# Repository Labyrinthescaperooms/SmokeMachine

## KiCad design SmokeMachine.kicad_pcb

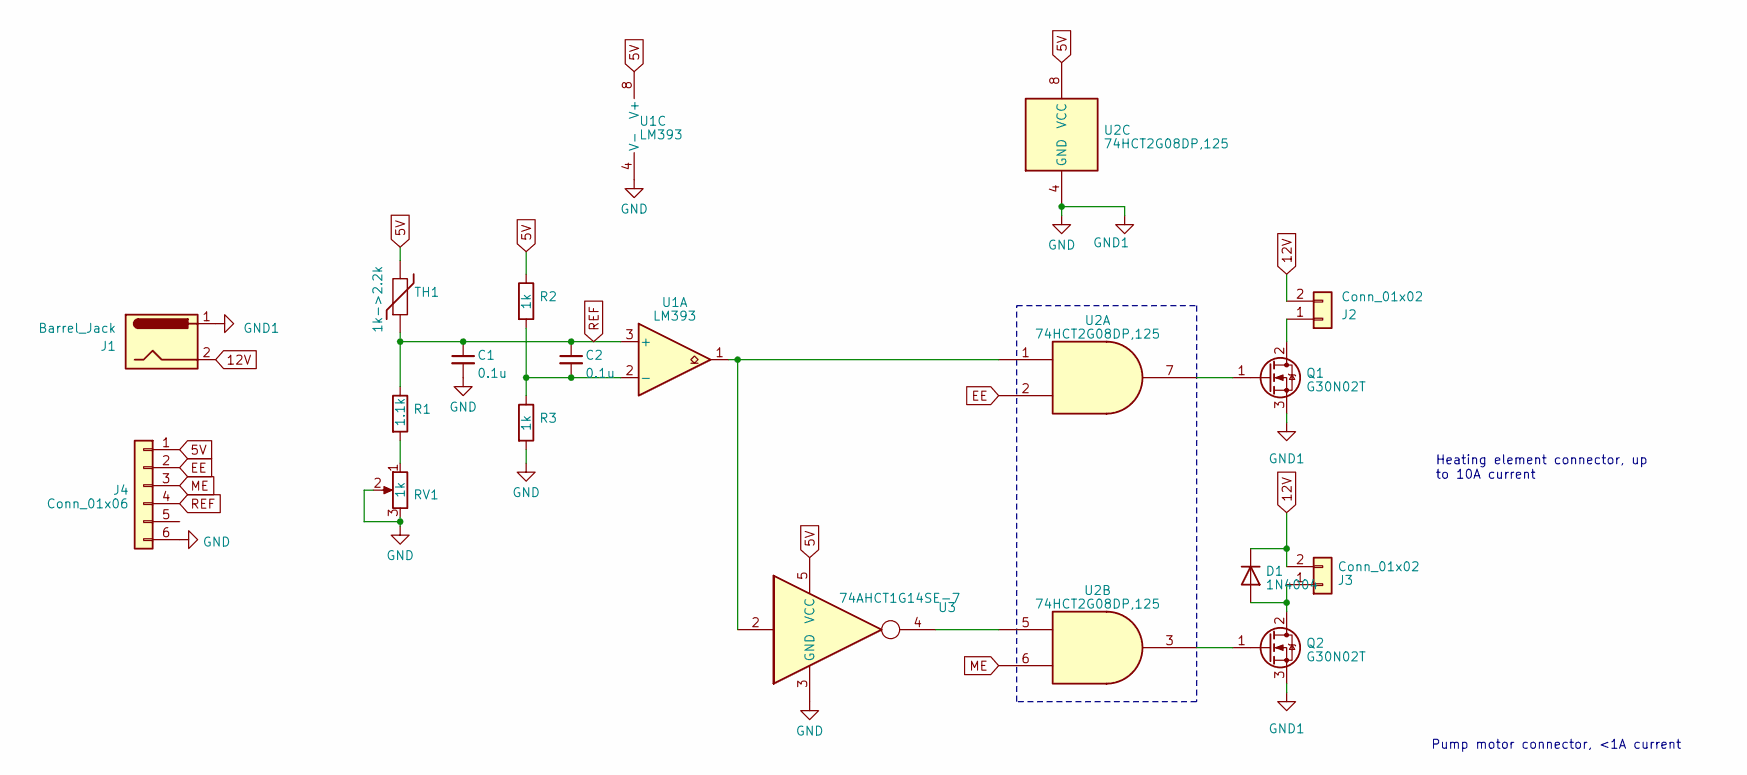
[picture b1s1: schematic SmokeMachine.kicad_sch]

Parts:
C1, C2: 0.1u; C_0805_2012Metric
D1: 1N4004; D_DO-41_SOD81_P10.16mm_Horizontal
J1: Barrel_Jack; mega-fit-1x2
J2, J3: Conn_01x02; mega-fit-1x2
J4: Conn_01x06; mini-lock-6x1-vert
Q1, Q2: G30N02T; TO-220-3_Vertical
R1: 1.1k; R_0805_2012Metric
R2, R3: 1k; R_0805_2012Metric
RV1: 1k; Potentiometer_Bourns_3296W_Vertical
TH1: 1k->2.2k; mini-lock-2x1-vert
U1: LM393; SOIC-8_3.9x4.9mm_P1.27mm
U2: 74HCT2G08DP,125; TSSOP-8_3x3mm_P0.65mm
U3: 74AHCT1G14SE-7; SOT-353_SC-70-5

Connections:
5V: J4.1, R2.1, TH1.2, U1.8 (V+), U2.8 (VCC), U3.5 (VCC)
12V: D1.1 (K), J1.2, J2.2, J3.2
EE: J4.2, U2.2
GND: C1.2, J1.1, J4.6, Q1.3 (S), Q2.3 (S), R3.2, RV1.2, RV1.3, U1.4 (V-), U2.4 (GND), U3.3 (GND)
ME: J4.3, U2.6
unnamed: D1.2 (A), J3.1, Q2.2 (D)
unnamed: J2.1, Q1.2 (D)
unnamed: Q1.1 (G), U2.7
unnamed: Q2.1 (G), U2.3
unnamed: R1.2, RV1.1
unnamed: U1.1, U2.1, U3.2
unnamed: C2.2, R2.2, R3.1, U1.2 (-)
unnamed: U2.5, U3.4
REF: C1.1, C2.1, J4.4, R1.1, TH1.1, U1.3 (+)

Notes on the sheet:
Heating element connector, up to 10A current
Pump motor connector, <1A current

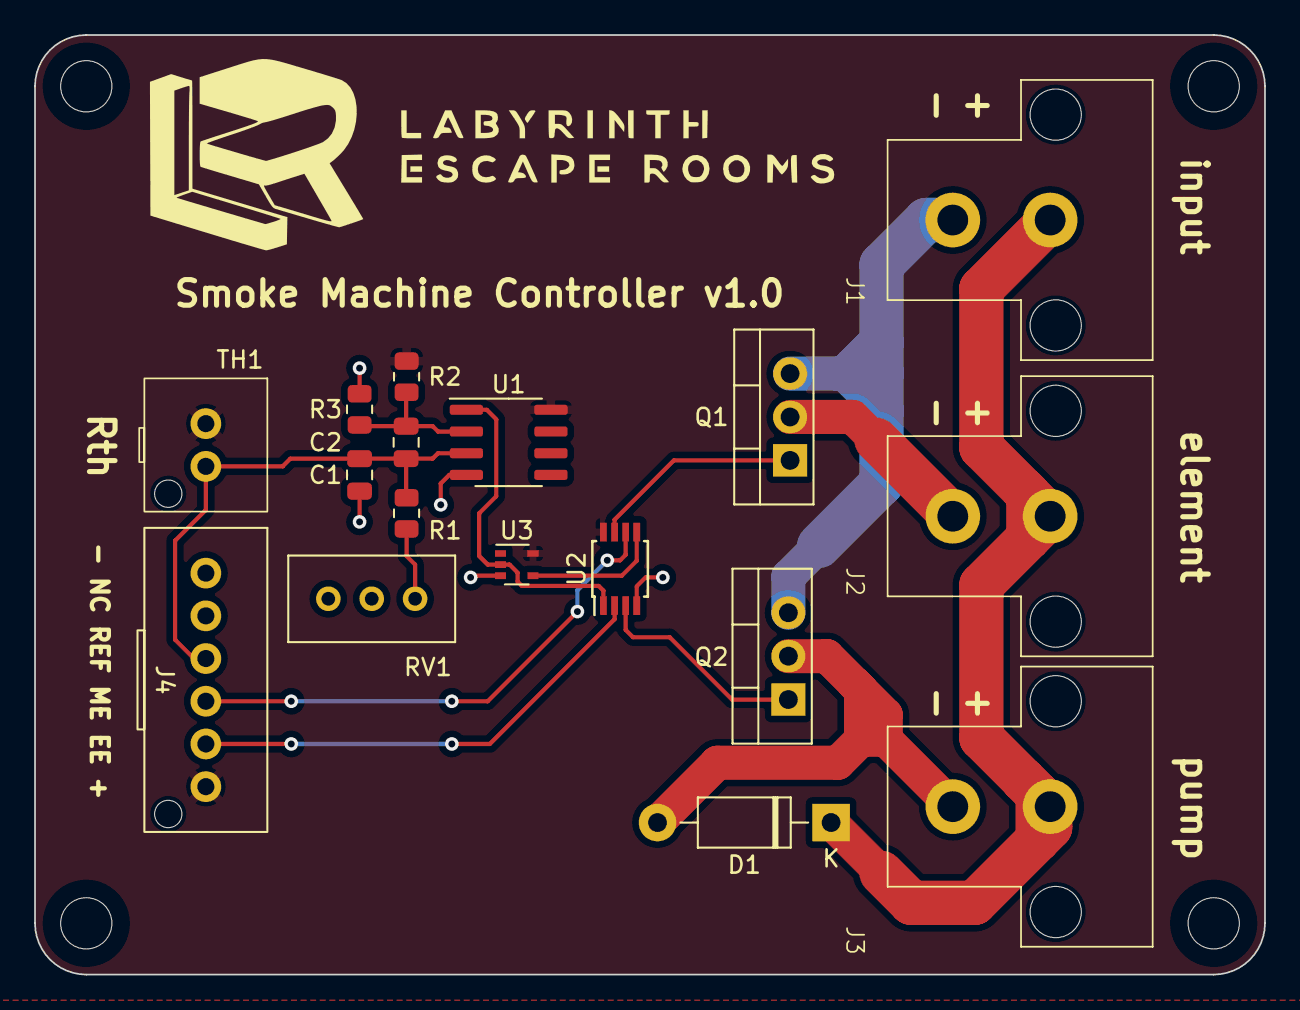
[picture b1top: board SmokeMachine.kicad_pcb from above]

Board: 2 copper layers, 72.0 x 55.0 mm, 17 parts (0 on the bottom side), 14 nets.

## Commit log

2023-04-05 added excel
2023-05-18 Updated calcs
2023-05-25 PCB layout
2023-06-07 Flyback diode
2023-11-27 PCB update
